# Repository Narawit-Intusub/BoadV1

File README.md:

# Modular LED Board V1

โครงการกระดานเกม LED แบบโมดูลาร์ จำนวนสูงสุด 4 บอร์ด:

- Master 1 บอร์ด
- Slave สูงสุด 3 บอร์ด
- พื้นที่เล่นบอร์ดละ 4×4 ช่อง
- LED บอร์ดละ 64 ดวง
- Unity ติดต่อ ESP32 ผ่าน Wi-Fi
- ESP32 ติดต่อ Master ATtiny1604 ผ่าน Logic Level Converter

อ่านรายละเอียดการออกแบบทั้งหมดได้ที่ [docs/V1_design_summary.md](docs/V1_design_summary.md)

---

## โครงสร้างโปรเจกต์ KiCad

โปรเจกต์นี้ได้รับการจัดโครงสร้างตามมาตรฐาน Multi-board Electronics Hardware:

```text
board game/
├── hardware/
│   ├── master/                 # บอร์ด Master (ESP32 + ATtiny1604 + LED Matrix 4x4)
│   │   ├── master.kicad_pro    # ไฟล์หลักสำหรับเปิดใน KiCad
│   │   ├── master.kicad_sch    # วงจร Schematic
│   │   ├── master.kicad_pcb    # เลย์เอาต์แผ่นวงจรพิมพ์ PCB
│   │   ├── sym-lib-table       # Symbol library mapping
│   │   └── fp-lib-table        # Footprint library mapping
│   ├── slave/                  # บอร์ด Slave (ATtiny1604 + LED Matrix 4x4)
│   │   ├── slave.kicad_pro     # ไฟล์หลักสำหรับเปิดใน KiCad
│   │   ├── slave.kicad_sch     # วงจร Schematic
│   │   ├── sym-lib-table       # Symbol library mapping
│   │   └── fp-lib-table        # Footprint library mapping
│   ├── rfid_addon/             # บอร์ดขยาย RFID Addon
│   │   ├── rfid_addon.kicad_pro
│   │   ├── rfid_addon.kicad_sch
│   │   ├── sym-lib-table
│   │   └── fp-lib-table
│   ├── libraries/              # Custom Symbols & Footprints รวมของโครงการ
│   │   ├── esp32-wemos-d1-mini/
│   │   ├── magnetic-connector/
│   │   ├── ws2812-matrix-2x2/
│   │   └── board_game_v1-cache.lib
│   └── experimental/           # โมเดลทดลอง / ทางเลือก (ESP32-only standalone variants)
│       ├── master_esp32/       # บอร์ดแม่แบบขับตรงด้วย ESP32 (ตัด ATtiny1604)
│       └── slave_esp32/        # บอร์ดลูกแบบใช้ ESP32 ประจำแผ่น
├── firmware/                   # ซอร์สโค้ดเฟิร์มแวร์ Arduino / megaTinyCore
│   ├── esp32_usb_bridge/       # ตัวส่งสัญญาณ USB Bridge (ESP-NOW)
│   ├── esp32_master_gateway/   # ตัวรับบนบอร์ดแม่ Master Gateway
│   ├── attiny1604_master/      # เฟิร์มแวร์เฉพาะบอร์ดแม่ ATtiny1604 (ID 0)
│   ├── attiny1604_slave/       # เฟิร์มแวร์บอร์ดลูก ATtiny1604 (Daisy-Chain Auto-Addressing)
│   └── esp32_rfid_addon/       # โมดูลอ่านการ์ด RFID Addon (ESP32 + RC522)
├── production/                 # ไฟล์สั่งผลิตแผ่นวงจรพิมพ์ (Gerber, ZIP, CNC G-code)
│   ├── fab_packages/           # ไฟล์ ZIP สำเร็จรูปสำหรับสั่งผลิต JLCPCB / PCBWay
│   ├── master_gerbers/         # ไฟล์ Gerber & Drill บอร์ด Master
│   ├── slave_gerbers/          # ไฟล์ Gerber & Drill บอร์ด Slave
│   ├── cnc_master/             # ไฟล์สำหรับกัด CNC บอร์ด Master (FlatCAM & G-code)
│   └── cnc_slave/              # ไฟล์สำหรับกัด CNC บอร์ด Slave
├── docs/                       # เอกสาร สรุปวงจร และไฟล์ Output
│   ├── pdf/                    # master.pdf, slave.pdf
│   ├── renders/                # ภาพ Render 3D และ SVG
│   ├── reports/                # ผลการตรวจ ERC / DRC
│   └── V1_design_summary.md    # รายละเอียดเชิงเทคนิคทั้งระบบ
├── README.md
└── .gitignore
```

### วิธีเปิดในโปรแกรม KiCad
เปิดโปรแกรม KiCad จากนั้นกด **File → Open Project** แล้วเลือกไฟล์โปรเจกต์ของแต่ละบอร์ดตามที่ต้องการ:
- **Master Board:** [hardware/master/master.kicad_pro](hardware/master/master.kicad_pro)
- **Slave Board:** [hardware/slave/slave.kicad_pro](hardware/slave/slave.kicad_pro)
- **RFID Addon Board:** [hardware/rfid_addon/rfid_addon.kicad_pro](hardware/rfid_addon/rfid_addon.kicad_pro)

---

## ข้อสรุปการออกแบบระบบ

- ใช้ Switching Power Supply 5V 30A แหล่งเดียว
- Master และ Slave ต่อ `5V/GND` แบบขนาน
- ไม่ใช้ Step-down บนแต่ละบอร์ด
- ESP32 รับไฟเข้าขา `5V/VCC` แต่ลอจิกยังเป็น 3.3V
- ระหว่าง ESP32 กับ ATtiny 5V ยังต้องใช้ Logic Level Converter 2 ช่อง
- ขั้วแม่เหล็กใช้ 6 พิน: `5V ×2`, `GND ×2`, `D0`, `D1`
- จำกัดความสว่างทุก Channel ไม่เกิน 50/255
- V1 ใช้ Unity เป็น Source of truth สำหรับตำแหน่งตัวละครและช่อง Action

## การต่อไฟระหว่างบอร์ด

ทุกบอร์ดต่อแบบขนาน:

```text
5V Power Supply
├─ Master
├─ Slave 1
├─ Slave 2
└─ Slave 3
```

ในทางกายภาพ Slave อาจรับไฟต่อผ่านขั้วแม่เหล็กของบอร์ดก่อนหน้า แต่เน็ต `+5V_BUS` และ `GND` ของทุกบอร์ดยังเป็นการต่อแบบขนาน ไม่ใช่อนุกรม

## การเปิด–ปิดและประกบบอร์ด

วิธีที่แนะนำคือปิด Main switch ก่อนเสียบหรือถอดขั้วแม่เหล็ก หากต้องทดลองขณะมีไฟ ให้ดับ LED หรือลดโหลดก่อน การมี TVS อย่างเดียวไม่ได้ทำให้ระบบรองรับ Hot-plug อย่างสมบูรณ์

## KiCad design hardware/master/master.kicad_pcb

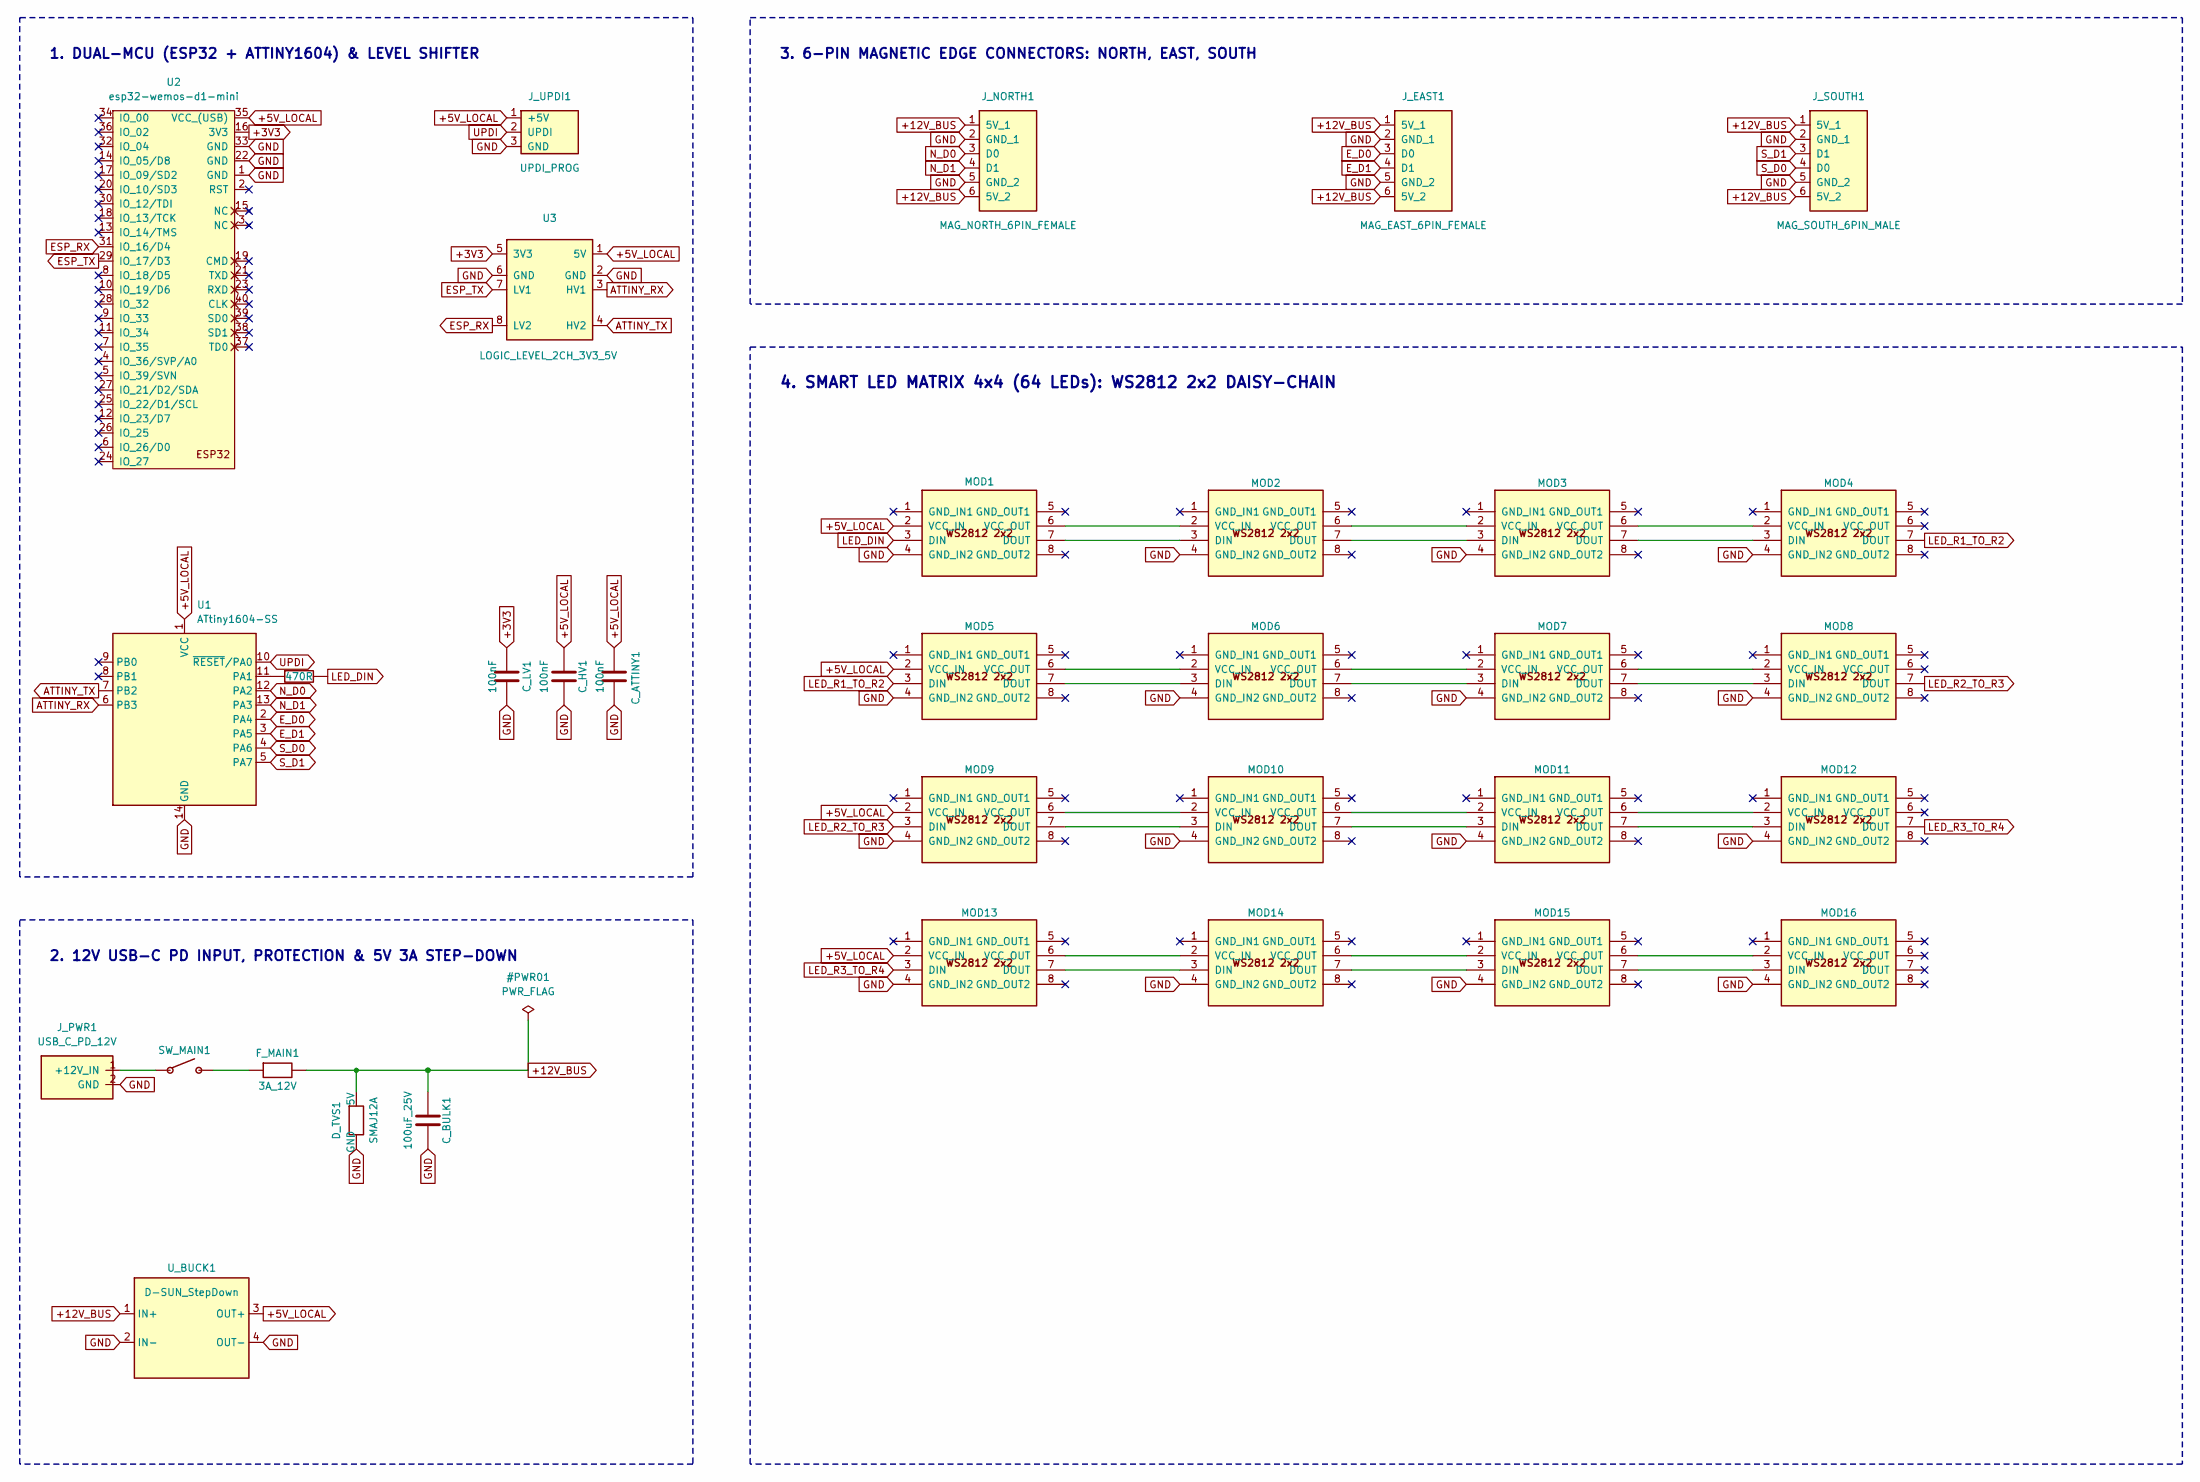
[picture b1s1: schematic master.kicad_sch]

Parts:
C_ATTINY1: 100nF; C_0603_1608Metric
C_BULK1: 100uF_25V; CP_Elec_6.3x7.7
C_HV1: 100nF; C_0603_1608Metric
C_LV1: 100nF; C_0603_1608Metric
D_TVS1: SMAJ12A; D_SMA
F_MAIN1: 3A_12V; Fuse_1206_3216Metric
J_EAST1: MAG_EAST_6PIN_FEMALE; fakemag6pin90degFemale
J_NORTH1: MAG_NORTH_6PIN_FEMALE; fakemag6pin90degFemale
J_PWR1: USB_C_PD_12V; usb-c-pd-ip2721
J_SOUTH1: MAG_SOUTH_6PIN_MALE; fakemag6pin90degMale
J_UPDI1: UPDI_PROG; pin-header-1x03-smd
MOD1, MOD2, MOD3, MOD4, MOD5, MOD6, MOD7, MOD8, MOD9, MOD10, MOD11, MOD12, MOD13, MOD14, MOD15, MOD16: WS2812_Matrix_2x2; WS2812_Matrix_2x2_15x15mm
R_LED1: 470R; R_0603_1608Metric
SW_MAIN1: SW_JST_XH_2P; JST_XH_B2B-XH-A_1x02_P2.50mm_Vertical
U1: ATtiny1604-SS; SOIC-14_3.9x8.7mm_P1.27mm
U2: esp32-wemos-d1-mini
U3: LOGIC_LEVEL_2CH_3V3_5V; logic-level-converter-2ch
U_BUCK1: D-SUN_StepDown; d-sun-stepdown

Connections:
+3V3: C_LV1.1, U2.16 (3V3), U3.5 (3V3)
+5V_LOCAL: C_ATTINY1.1, C_HV1.1, J_UPDI1.1 (+5V), MOD1.2 (VCC_IN), MOD5.2 (VCC_IN), MOD9.2 (VCC_IN), MOD13.2 (VCC_IN), U1.1 (VCC), U2.35 (VCC_(USB)), U3.1 (5V), U_BUCK1.3 (OUT+)
+12V_BUS: C_BULK1.1, D_TVS1.1 (5V), F_MAIN1.2, J_EAST1.1 (5V_1), J_EAST1.6 (5V_2), J_NORTH1.1 (5V_1), J_NORTH1.6 (5V_2), J_SOUTH1.1 (5V_1), J_SOUTH1.6 (5V_2), U_BUCK1.1 (IN+)
ATTINY_RX: U1.6 (PB3), U3.3 (HV1)
ATTINY_TX: U1.7 (PB2), U3.4 (HV2)
ESP_RX: U2.31 (IO_16/D4), U3.8 (LV2)
ESP_TX: U2.29 (IO_17/D3), U3.7 (LV1)
E_D0: J_EAST1.3 (D0), U1.2 (PA4)
E_D1: J_EAST1.4 (D1), U1.3 (PA5)
GND: C_ATTINY1.2, C_BULK1.2, C_HV1.2, C_LV1.2, D_TVS1.2 (GND), J_EAST1.2 (GND_1), J_EAST1.5 (GND_2), J_NORTH1.2 (GND_1), J_NORTH1.5 (GND_2), J_PWR1.2 (GND), J_SOUTH1.2 (GND_1), J_SOUTH1.5 (GND_2), J_UPDI1.3 (GND), MOD1.4 (GND_IN2), MOD2.4 (GND_IN2), MOD3.4 (GND_IN2), MOD4.4 (GND_IN2), MOD5.4 (GND_IN2), MOD6.4 (GND_IN2), MOD7.4 (GND_IN2), MOD8.4 (GND_IN2), MOD9.4 (GND_IN2), MOD10.4 (GND_IN2), MOD11.4 (GND_IN2), MOD12.4 (GND_IN2), MOD13.4 (GND_IN2), MOD14.4 (GND_IN2), MOD15.4 (GND_IN2), MOD16.4 (GND_IN2), U1.14 (GND), U2.1 (GND), U2.22 (GND), U2.33 (GND), U3.2 (GND), U3.6 (GND), U_BUCK1.2 (IN-), U_BUCK1.4 (OUT-)
LED_DIN: MOD1.3 (DIN), R_LED1.2
LED_R1_TO_R2: MOD4.7 (DOUT), MOD5.3 (DIN)
LED_R2_TO_R3: MOD8.7 (DOUT), MOD9.3 (DIN)
LED_R3_TO_R4: MOD12.7 (DOUT), MOD13.3 (DIN)
N_D0: J_NORTH1.3 (D0), U1.12 (PA2)
N_D1: J_NORTH1.4 (D1), U1.13 (PA3)
unnamed: F_MAIN1.1, SW_MAIN1.2
unnamed: J_PWR1.1 (+12V_IN), SW_MAIN1.1
unnamed: MOD1.7 (DOUT), MOD2.3 (DIN)
unnamed: MOD1.6 (VCC_OUT), MOD2.2 (VCC_IN)
unnamed: MOD2.7 (DOUT), MOD3.3 (DIN)
unnamed: MOD2.6 (VCC_OUT), MOD3.2 (VCC_IN)
unnamed: MOD3.7 (DOUT), MOD4.3 (DIN)
unnamed: MOD3.6 (VCC_OUT), MOD4.2 (VCC_IN)
unnamed: MOD5.7 (DOUT), MOD6.3 (DIN)
unnamed: MOD5.6 (VCC_OUT), MOD6.2 (VCC_IN)
unnamed: MOD6.7 (DOUT), MOD7.3 (DIN)
unnamed: MOD6.6 (VCC_OUT), MOD7.2 (VCC_IN)
unnamed: MOD7.7 (DOUT), MOD8.3 (DIN)
unnamed: MOD7.6 (VCC_OUT), MOD8.2 (VCC_IN)
unnamed: MOD9.7 (DOUT), MOD10.3 (DIN)
unnamed: MOD10.7 (DOUT), MOD11.3 (DIN)
unnamed: MOD9.6 (VCC_OUT), MOD10.2 (VCC_IN)
unnamed: MOD10.6 (VCC_OUT), MOD11.2 (VCC_IN)
unnamed: MOD11.7 (DOUT), MOD12.3 (DIN)
unnamed: MOD11.6 (VCC_OUT), MOD12.2 (VCC_IN)
unnamed: MOD13.7 (DOUT), MOD14.3 (DIN)
unnamed: MOD13.6 (VCC_OUT), MOD14.2 (VCC_IN)
unnamed: MOD14.7 (DOUT), MOD15.3 (DIN)
unnamed: MOD14.6 (VCC_OUT), MOD15.2 (VCC_IN)
unnamed: MOD15.7 (DOUT), MOD16.3 (DIN)
unnamed: MOD15.6 (VCC_OUT), MOD16.2 (VCC_IN)
unnamed: R_LED1.1, U1.11 (PA1)
S_D0: J_SOUTH1.4 (D0), U1.4 (PA6)
S_D1: J_SOUTH1.3 (D1), U1.5 (PA7)
UPDI: J_UPDI1.2 (UPDI), U1.10 (~RESET/PA0)

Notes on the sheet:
1. DUAL-MCU (ESP32 + ATTINY1604) & LEVEL SHIFTER
2. 12V USB-C PD INPUT, PROTECTION & 5V 3A STEP-DOWN
3. 6-PIN MAGNETIC EDGE CONNECTORS: NORTH, EAST, SOUTH
4. SMART LED MATRIX 4x4 (64 LEDs): WS2812 2x2 DAISY-CHAIN

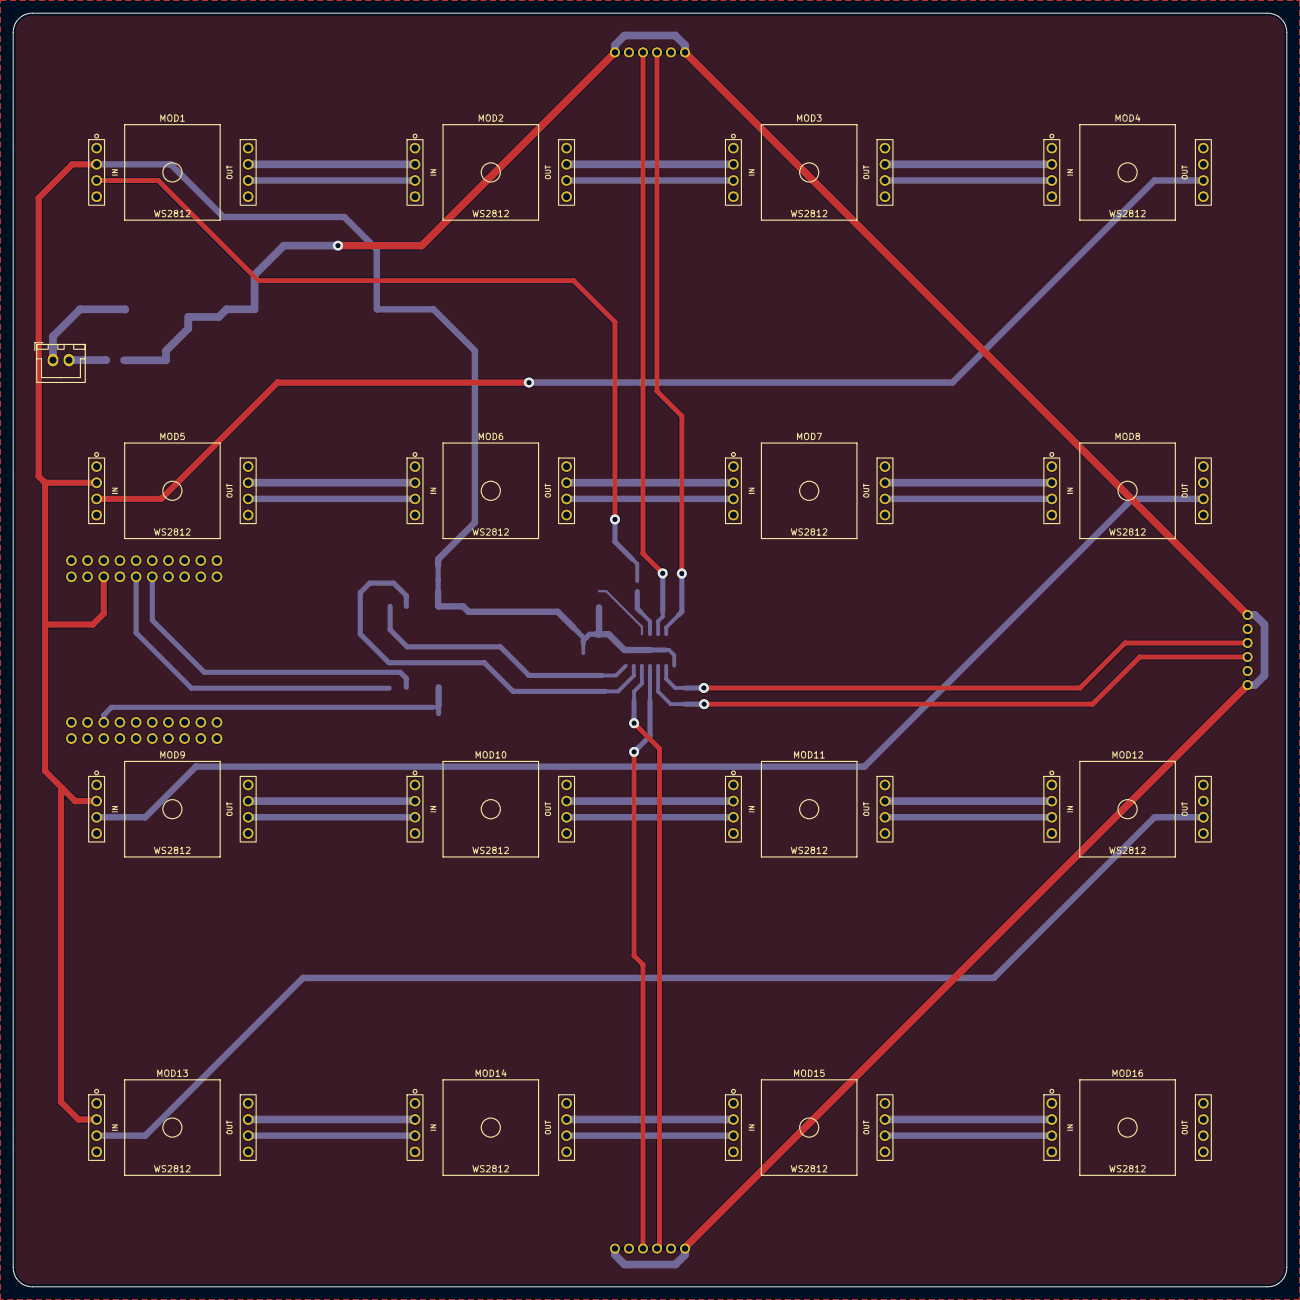
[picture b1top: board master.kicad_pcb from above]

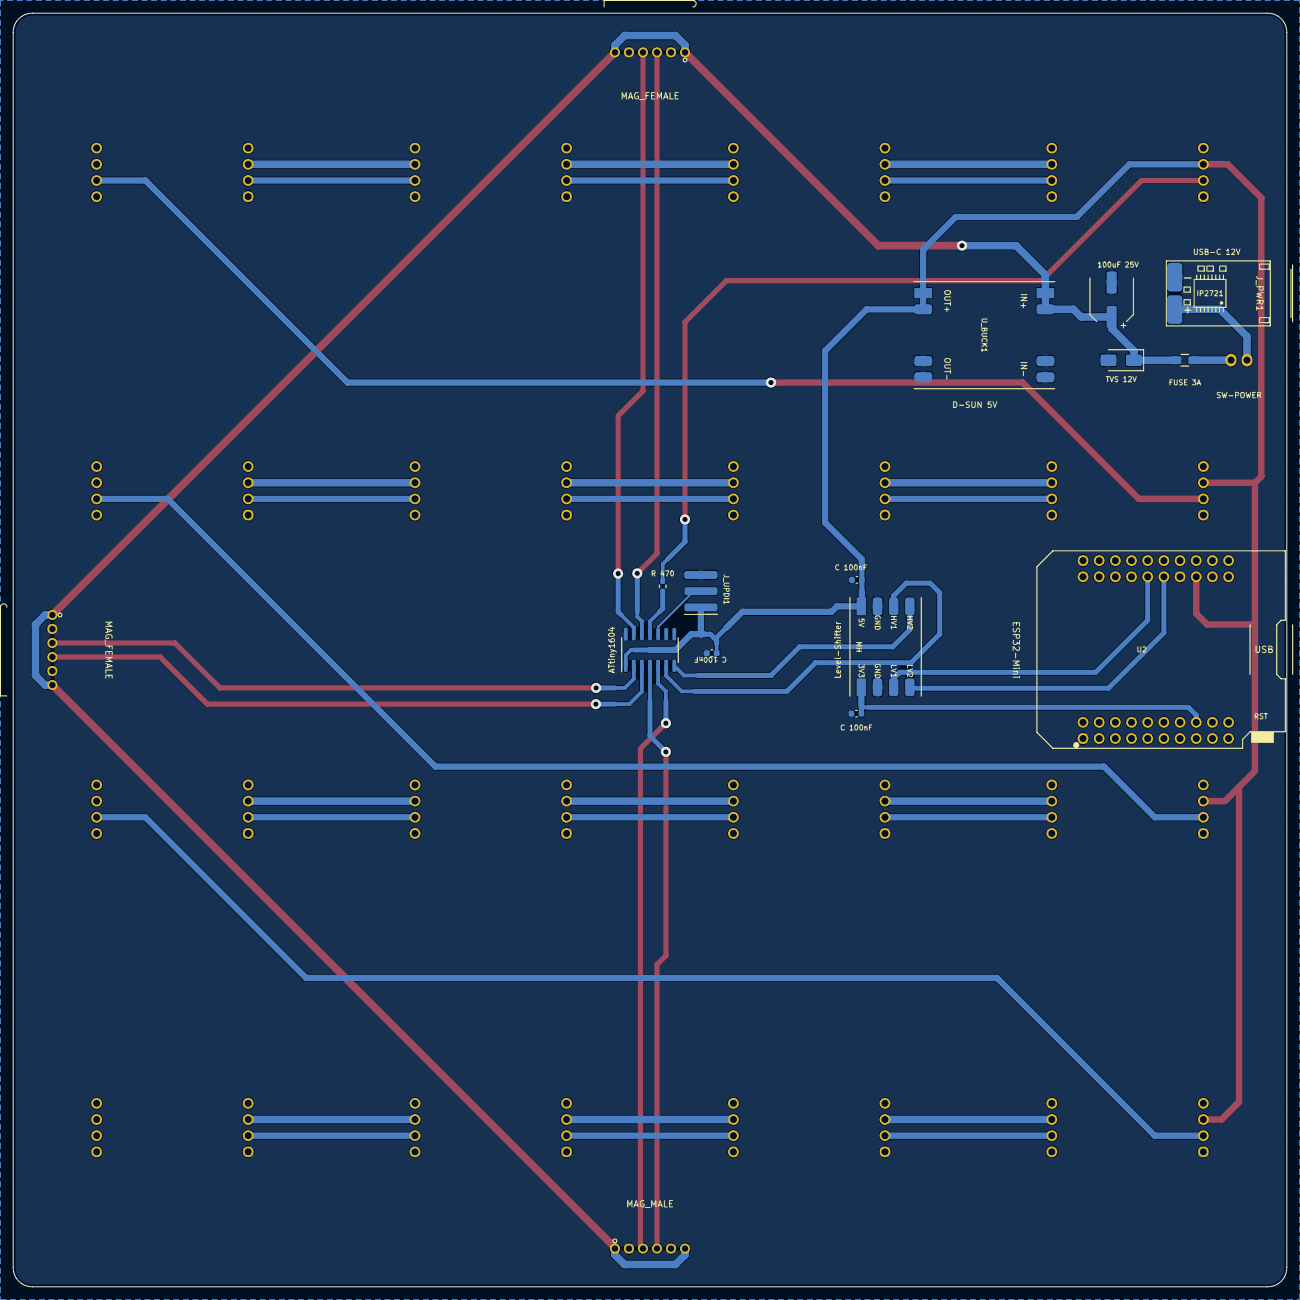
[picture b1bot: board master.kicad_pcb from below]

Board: 2 copper layers, 200.0 x 200.0 mm, 33 parts (16 on the bottom side), 46 nets.

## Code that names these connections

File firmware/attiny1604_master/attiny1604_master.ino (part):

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 *   - ID ประจำแผ่น: กำหนดตายตัวเป็น 0 (Master Tile)
 * 
 * Pin Assignment ที่ตรงกับแผ่น Master PCB 100%:
 *   - PA1 (Pin 11) : LED_DIN ขับหลอดไฟ WS2812B ทั้ง 64 ดวง (ผ่าน R 470 โอห์ม R_LED1)
 *   - PB3 (Pin 6)  : ATTINY_RX รับข้อมูล UART จาก ESP32 (TX GPIO17) ผ่าน Level Shifter
 *   - PB2 (Pin 7)  : ATTINY_TX ส่งข้อมูล UART กลับ ESP32 (RX GPIO16) ผ่าน Level Shifter
 *   - PA4 (Pin 2)  : E_D0 (East Pin 3) ขาส่งต่อ UART Daisy-Chain ไปยังแผ่นลูกแผ่นแรก (Slave 1)
 *   - PA5 (Pin 3)  : E_D1 (East Pin 4) ขารับสัญญาณ Presence Detect จากแผ่นลูก (INPUT_PULLUP)
 *   - PA0 (Pin 10) : UPDI สำหรับโปรแกรมชิป (J_UPDI1)
 *   - ขั้วตรวจจับเพื่อนบ้าน (Neighbor Sensing):
 *     * North (Side 0) : PA2 (N_D0, Pin 12 - INPUT_PULLUP), PA3 (N_D1, Pin 13 - OUTPUT LOW)
 *     * East  (Side 1) : PA4 (E_D0, Pin 2 / TX), PA5 (E_D1, Pin 3 - INPUT_PULLUP)
 *     * South (Side 2) : PA6 (S_D0, Pin 4 - INPUT_PULLUP), PA7 (S_D1, Pin 5 - OUTPUT LOW)
 *     * (Master ไม่มีขั้ว West)
 * 
 * บทบาทหน้าที่ (Pure Hardware LED Driver & Daisy-Chain Router - แฟลชครั้งเดียวจบ):
 *   1. รับค่าสี RGB 48 ไบต์ที่คำนวณความสว่างและพิกัดมาจาก ESP32 Master Gateway แล้วเก็บเข้า Back Buffer (Double Buffering)
 *   2. เมื่อได้รับคำสั่ง PKT_FRAME_COMMIT (0x03) จะสลับเข้า Active Buffer แล้วขับไฟ WS2812B 64 ดวงผ่าน tinyNeoPixel_Static ทันที
 *   3. Daisy-Chain Router: หากแพ็กเก็ตระบุปลายทางเป็นแผ่นลูก (dest != 0 หรือ Broadcast 0xFF) จะส่งต่อออกขา East PA4 ด้วยความเร็ว 115200 bps
 *   4. Auto-Addressing & Hot-Plug: แจก ID 1 ให้แผ่นลูกแผ่นแรกอัตโนมัติทันทีที่ตรวจพบการเสียบขั้วแม่เหล็ก East (PIN_E_D1)
 *   5. การปรับความสว่าง ทิศทางกระดาน หรือลอจิกเกมทั้งหมด ถูกจัดการที่ฝั่ง ESP32 (Gateway / USB Bridge) 100% จึงไม่ต้องกลับมาแก้ไขหรือแฟลชชิป ATtiny1604 ซ้ำอีก
 * ============================================================================
 */
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// ============================================================================
//                         PIN & HARDWARE DEFINITIONS
// ============================================================================
#define LED_PIN             PIN_PA1  // ขาขับหลอด WS2812B ผ่าน R 470 โอห์ม
#define FORWARD_TX_PIN      PIN_PA4  // East D0: ขาส่งต่อ UART ไปยัง Slave แผ่นถัดไป
#define PIN_E_D1            PIN_PA5  // East D1: ตรวจจับการเสียบแผ่นลูก (Presence Detect)

// ขั้วตรวจจับทิศเหนือและทิศใต้
#define PIN_N_D0            PIN_PA2  // North D0 (INPUT_PULLUP)
#define PIN_N_D1            PIN_PA3  // North D1 (OUTPUT LOW)
#define PIN_S_D0            PIN_PA6  // South D0 (INPUT_PULLUP)
#define PIN_S_D1            PIN_PA7  // South D1 (OUTPUT LOW)

// ============================================================================
//                             CONFIGURATIONS
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// ตรวจสอบการประกบของขั้วแม่เหล็ก
uint8_t readConnectedSides() {
    uint8_t sides = 0;
    if (!digitalRead(PIN_N_D0)) sides |= (1 << 0); // North
    if (!digitalRead(PIN_E_D1)) sides |= (1 << 1); // East (มี Slave เสียบอยู่)
    if (!digitalRead(PIN_S_D0)) sides |= (1 << 2); // South
    // Master ไม่มี West
    return sides;
}
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    strip.show();
}

// ส่งไบต์แบบ Bit-Bang UART (115200 bps, 8.68 us/bit) ออกขา East PA4
// ใช้ Direct Port Register (PORTA.OUTSET / OUTCLR = 1 ลูกคลื่นสัญญาณนาฬิกา) แทน digitalWrite()
// เพื่อป้องกัน Baud Rate เพี้ยนที่ความเร็ว 115200 bps บนชิป 16/20 MHz
void txBitBangByte(uint8_t b) {
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    txBitBangByte(crc);
}

// ส่งแพ็กเก็ตตอบกลับ ESP32 ทาง Hardware USART0 PB2 TX
void sendPacketUpstream(uint8_t type, uint8_t src, uint8_t dest, uint8_t seq, uint8_t frame, uint8_t ttl, const uint8_t *data, uint8_t len) {
    Serial.write(START_BYTE);
    Serial.write(type);
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//                                SETUP
// ============================================================================
void setup() {
    // 1. ล็อคพินมาตรฐาน USART0 (PB3=RX, PB2=TX) และเริ่มต้นที่ 115200 bps (8-N-1) เพื่อสื่อสารกับ ESP32
    Serial.swap(0);
    Serial.begin(115200);

    // 2. ขาส่งต่อ UART ไปยัง Slave 1 (East D0 / PA4)
    pinMode(FORWARD_TX_PIN, OUTPUT);
    digitalWrite(FORWARD_TX_PIN, HIGH);

    // 3. กำหนดโหมดพินตรวจจับขั้วแม่เหล็ก
    pinMode(PIN_E_D1, INPUT_PULLUP); // รับสัญญาณ Presence Detect จากแผ่นลูก (PB2)

    pinMode(PIN_N_D0, INPUT_PULLUP);
    pinMode(PIN_N_D1, OUTPUT); digitalWrite(PIN_N_D1, LOW);

    pinMode(PIN_S_D0, INPUT_PULLUP);
    pinMode(PIN_S_D1, OUTPUT); digitalWrite(PIN_S_D1, LOW);

    // 4. เริ่มต้นไฟ NeoPixel 64 ดวง
    pinMode(LED_PIN, OUTPUT);
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    // Dynamic Hot-Plug: ตรวจจับการเสียบแผ่นลูกแผ่นแรกสดๆ ทางทิศ East
    // ------------------------------------------------------------------------
    static uint8_t lastEastConnected = 0;
    uint8_t eastConnected = !digitalRead(PIN_E_D1);
    if (eastConnected && !lastEastConnected) {
        delay(50); // หน่วงเวลารอไฟและหน้าสัมผัสของแผ่นลูกนิ่ง
        uint8_t firstSlaveId = 1;
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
